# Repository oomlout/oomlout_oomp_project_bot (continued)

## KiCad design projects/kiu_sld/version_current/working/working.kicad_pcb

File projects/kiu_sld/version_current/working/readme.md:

# sld by kiu  
This is a harvested standardized copy of a project from github.  
The original project can be found at:  
https://github.com/kiu/sld  
Please consult that link for additional, details, files, and license information.  
Note: It was auto harvested and if the original repo had more than one board file or anything out of the ordinary the files here are likely not representative.

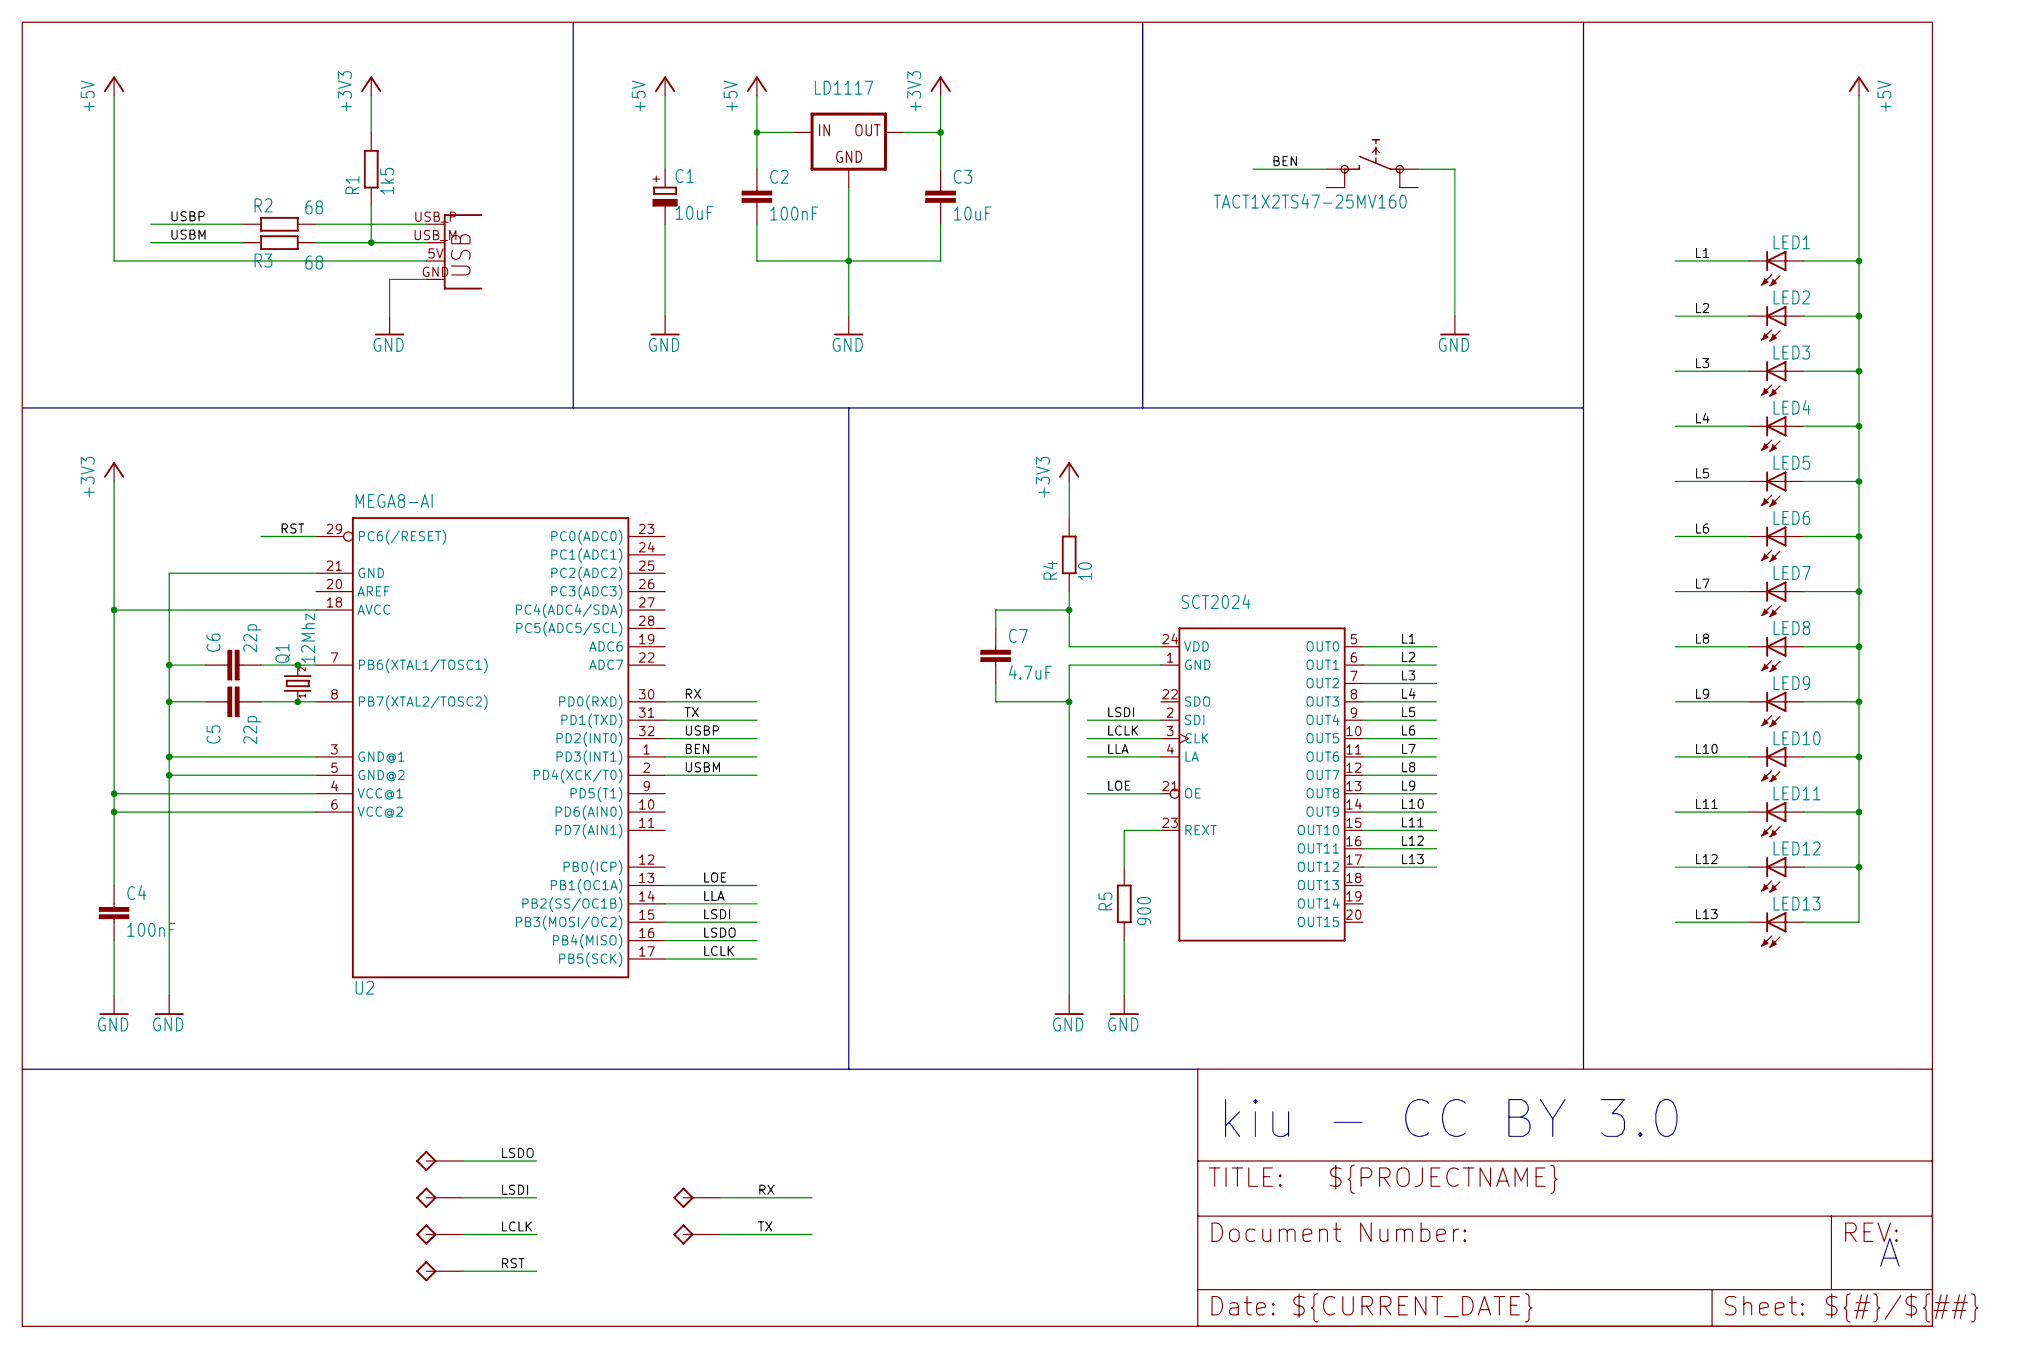
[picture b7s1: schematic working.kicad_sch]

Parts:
C1: 10uF; CT3216
C2, C4: 100nF; C0805
C3: 10uF; C0805
C5, C6: 22p; C0805
C7: 4.7uF; C0805
JP1: USBPCB; USB-A-PCB
LED1, LED2, LED3, LED4, LED5, LED6, LED7, LED8, LED9, LED10, LED11, LED12, LED13: LEDKA-3528ASYC; KA-3528ASYC
Q1: 12Mhz; HC49UP
R1: 1k5; R0805
R2, R3: 68; R0805
R4: 10; R0805
R5: 900; R0805
S1: TACT1X2TS47-25MV160; TACT1.7X5.15
T1, T2, T3, T4, T5, T6: PAD; PAD-1X1
U1: LD1117; SOT223
U2: MEGA8-AI; TQFP32-08
U3: SCT2024; SSOP24

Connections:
+3V3: C3.1, C4.1, R1.2, R4.2, U1.2 (OUT), U2.4 (VCC@1), U2.6 (VCC@2), U2.18 (AVCC)
+5V: C1.+, C2.1, JP1.5V (VBUS), LED1.A, LED2.A, LED3.A, LED4.A, LED5.A, LED6.A, LED7.A, LED8.A, LED9.A, LED10.A, LED11.A, LED12.A, LED13.A, U1.3 (IN)
BEN: S1.2 (1@A), U2.1 (PD3(INT1))
GND: C1.-, C2.2, C3.2, C4.2, C5.1, C6.1, C7.2, JP1.GND, R5.2, S1.1 (0@A), U1.1 (GND), U2.3 (GND@1), U2.5 (GND@2), U2.21 (GND), U3.1 (GND)
L1: LED1.C, U3.5 (OUT0)
L2: LED2.C, U3.6 (OUT1)
L3: LED3.C, U3.7 (OUT2)
L4: LED4.C, U3.8 (OUT3)
L5: LED5.C, U3.9 (OUT4)
L6: LED6.C, U3.10 (OUT5)
L7: LED7.C, U3.11 (OUT6)
L8: LED8.C, U3.12 (OUT7)
L9: LED9.C, U3.13 (OUT8)
L10: LED10.C, U3.14 (OUT9)
L11: LED11.C, U3.15 (OUT10)
L12: LED12.C, U3.16 (OUT11)
L13: LED13.C, U3.17 (OUT12)
LCLK: T3.P1, U2.17 (PB5(SCK)), U3.3 (CLK)
LLA: U2.14 (PB2(SS/OC1B)), U3.4 (LA)
LOE: U2.13 (PB1(OC1A)), U3.21 (OE)
LSDI: T2.P1, U2.15 (PB3(MOSI/OC2)), U3.2 (SDI)
LSDO: T1.P1, U2.16 (PB4(MISO))
unnamed: C6.2, Q1.2, U2.7 (PB6(XTAL1/TOSC1))
unnamed: C5.2, Q1.1, U2.8 (PB7(XTAL2/TOSC2))
unnamed: R5.1, U3.23 (REXT)
unnamed: C7.1, R4.1, U3.24 (VDD)
unnamed: JP1.USB_P (D+), R2.2
unnamed: JP1.USB_M (D-), R1.1, R3.1
RST: T4.P1, U2.29 (PC6(/RESET))
RX: T5.P1, U2.30 (PD0(RXD))
TX: T6.P1, U2.31 (PD1(TXD))
USBM: R3.2, U2.2 (PD4(XCK/T0))
USBP: R2.1, U2.32 (PD2(INT0))

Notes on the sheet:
kiu - CC BY 3.0

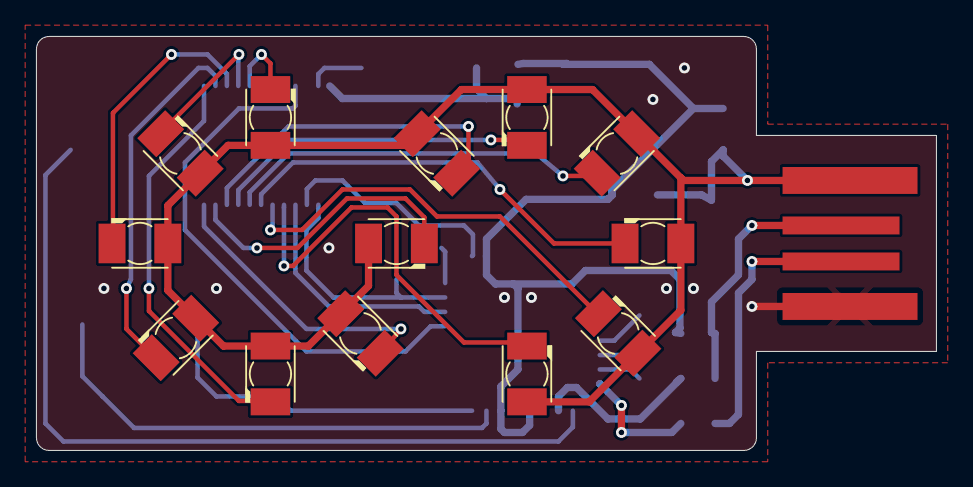
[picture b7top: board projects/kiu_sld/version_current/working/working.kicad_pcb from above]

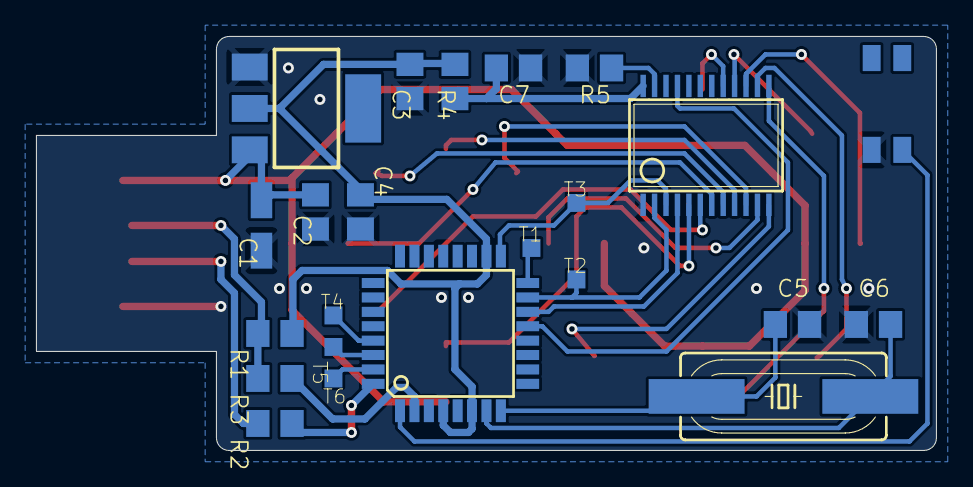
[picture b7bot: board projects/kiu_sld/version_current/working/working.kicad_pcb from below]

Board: 2 copper layers, 50.0 x 23.0 mm, 37 parts (23 on the bottom side), 33 nets.

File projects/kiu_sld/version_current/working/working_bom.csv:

"Id";"Designator";"Footprint";"Quantity";"Designation";"Supplier and ref";
1;"LED5,LED12,LED3,LED9,LED6,LED13,LED11,LED10,LED4,LED2,LED8,LED1,LED7";"KA-3528ASYC";13;"";;;
2;"JP1";"USB-A-PCB";1;"USBPCB";;;
3;"T2,T1,T4,T6,T3,T5";"PAD-1X1";6;"PAD";;;
4;"U2";"TQFP32-08";1;"MEGA8-AI";;;
5;"R1";"R0805";1;"1k5";;;
6;"R2,R3";"R0805";2;"68";;;
7;"C2,C4";"C0805";2;"100nF";;;
8;"U3";"SSOP24";1;"SCT2024";;;
9;"C1";"CT3216";1;"10uF";;;
10;"S1";"TACT1.7X5.15";1;"TACT1X2TS47-25MV160";;;
11;"C7";"C0805";1;"4.7uF";;;
12;"C6,C5";"C0805";2;"22p";;;
13;"C3";"C0805";1;"10uF";;;
14;"R4";"R0805";1;"10";;;
15;"Q1";"HC49UP";1;"12Mhz";;;
16;"R5";"R0805";1;"900";;;
17;"U1";"SOT223";1;"LD1117";;;
